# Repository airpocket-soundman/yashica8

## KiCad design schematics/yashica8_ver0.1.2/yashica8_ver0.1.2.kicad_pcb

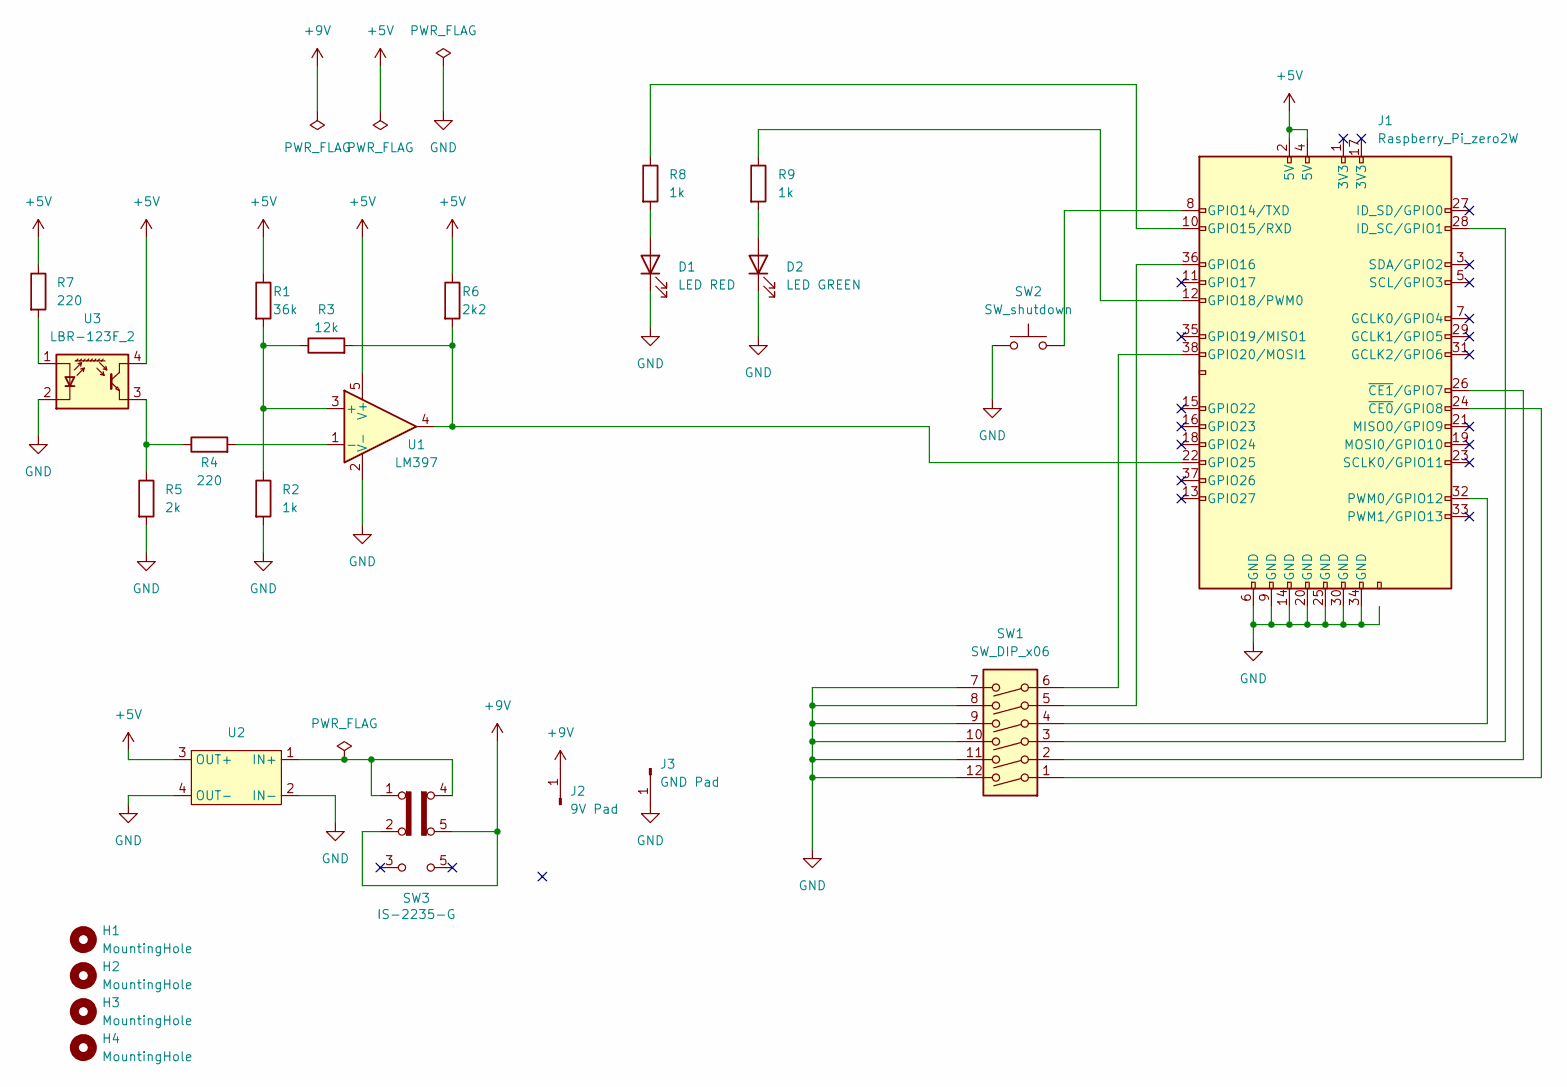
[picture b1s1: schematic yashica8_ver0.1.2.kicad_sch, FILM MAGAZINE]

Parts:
D1: LED RED; LED_D3.0mm
D2: LED GREEN; LED_D3.0mm
H1, H2, H3, H4: MountingHole; MountingHole_2.1mm
J1: Raspberry_Pi_zero2W; raspberry Pi socket 2x19
J2: 9V Pad; SolderWirePad_1x01_SMD_1x2mm
J3: GND Pad; SolderWirePad_1x01_SMD_1x2mm
R1: 36k; R_0805_2012Metric_Pad1.20x1.40mm_HandSolder
R2, R8, R9: 1k; R_0805_2012Metric_Pad1.20x1.40mm_HandSolder
R3: 12k; R_0805_2012Metric_Pad1.20x1.40mm_HandSolder
R4, R7: 220; R_0805_2012Metric_Pad1.20x1.40mm_HandSolder
R5: 2k; R_0805_2012Metric_Pad1.20x1.40mm_HandSolder
R6: 2k2; R_0805_2012Metric_Pad1.20x1.40mm_HandSolder
SW1: SW_DIP_x06; SW_DIP_SPSTx06_Slide_9.78x17.42mm_W7.62mm_P2.54mm
SW2: SW_shutdown; SW_PUSH_6mm
SW3: IS-2235-G
U1: LM397; SOT-23-5
U2: MP2307 DC-DC Board
U3: LBR-123F_2

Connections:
+5V: J1.2 (5V), J1.4 (5V), R1.1, R6.1, R7.1, U1.5 (V+), U2.3 (OUT+), U3.4
+9V: J2.1, SW3.2 (B), SW3.5 (B)
GND: D1.1 (K), D2.1 (K), J1.6 (GND), J1.9 (GND), J1.14 (GND), J1.20 (GND), J1.25 (GND), J1.30 (GND), J1.34 (GND), J3.1, R2.2, R5.2, SW1.7, SW1.8, SW1.9, SW1.10, SW1.11, SW1.12, SW2.1, U1.2 (V-), U2.2 (IN-), U2.4 (OUT-), U3.2 (K)
unnamed: D1.2 (A), R8.2
unnamed: D2.2 (A), R9.2
unnamed: J1.8 (GPIO14/TXD), SW2.2
unnamed: J1.10 (GPIO15/RXD), R8.1
unnamed: J1.36 (GPIO16), SW1.5
unnamed: J1.12 (GPIO18/PWM0), R9.1
unnamed: J1.38 (GPIO20/MOSI1), SW1.6
unnamed: J1.22 (GPIO25), R3.2, R6.2, U1.4
unnamed: J1.28 (ID_SC/GPIO1), SW1.3
unnamed: J1.32 (PWM0/GPIO12), SW1.4
unnamed: J1.24 (~CE0/GPIO8), SW1.1
unnamed: J1.26 (~CE1/GPIO7), SW1.2
unnamed: R4.1, R5.1, U3.3
unnamed: R1.2, R2.1, R3.1, U1.3 (+)
unnamed: R4.2, U1.1 (-)
unnamed: SW3.1 (A), SW3.4 (C), U2.1 (IN+)
unnamed: R7.2, U3.1 (A)

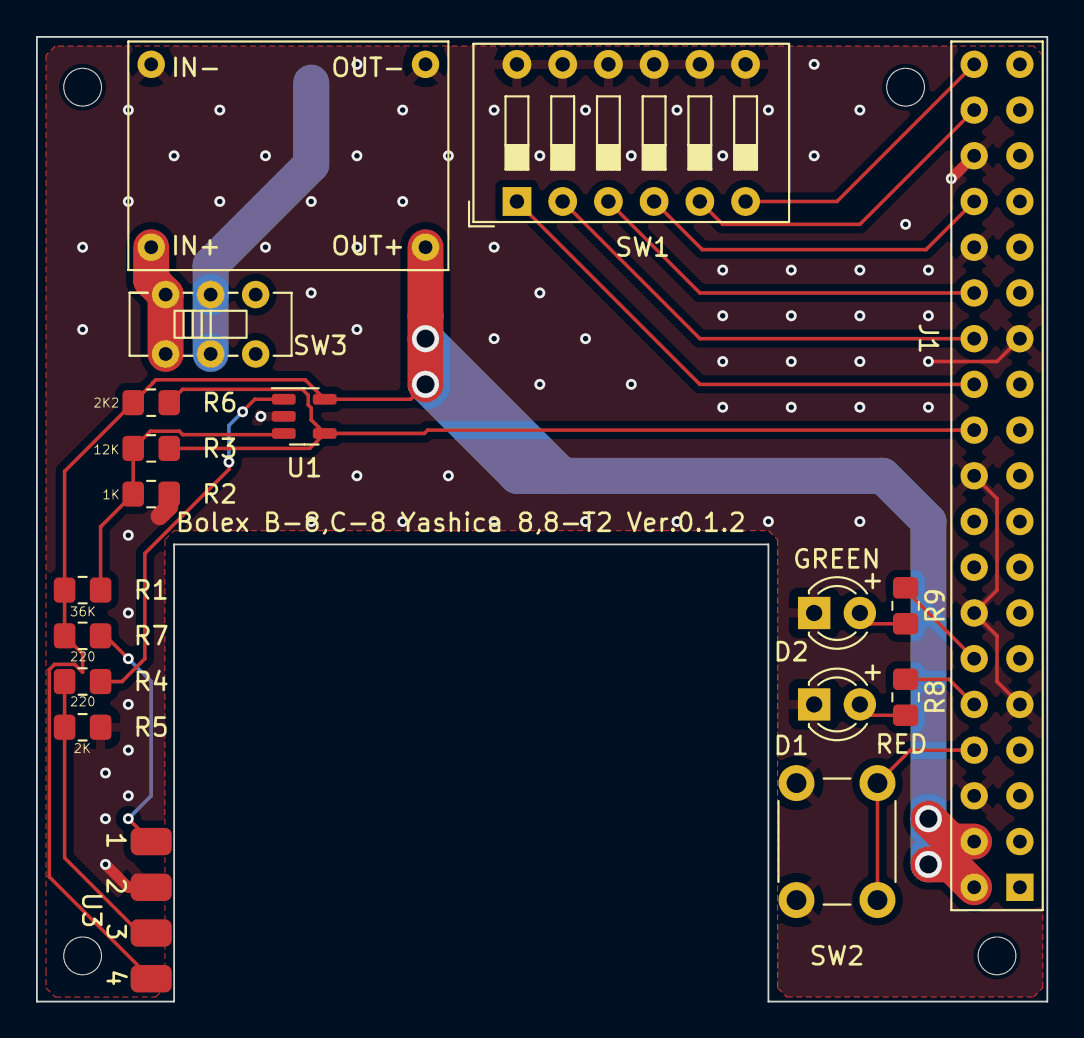
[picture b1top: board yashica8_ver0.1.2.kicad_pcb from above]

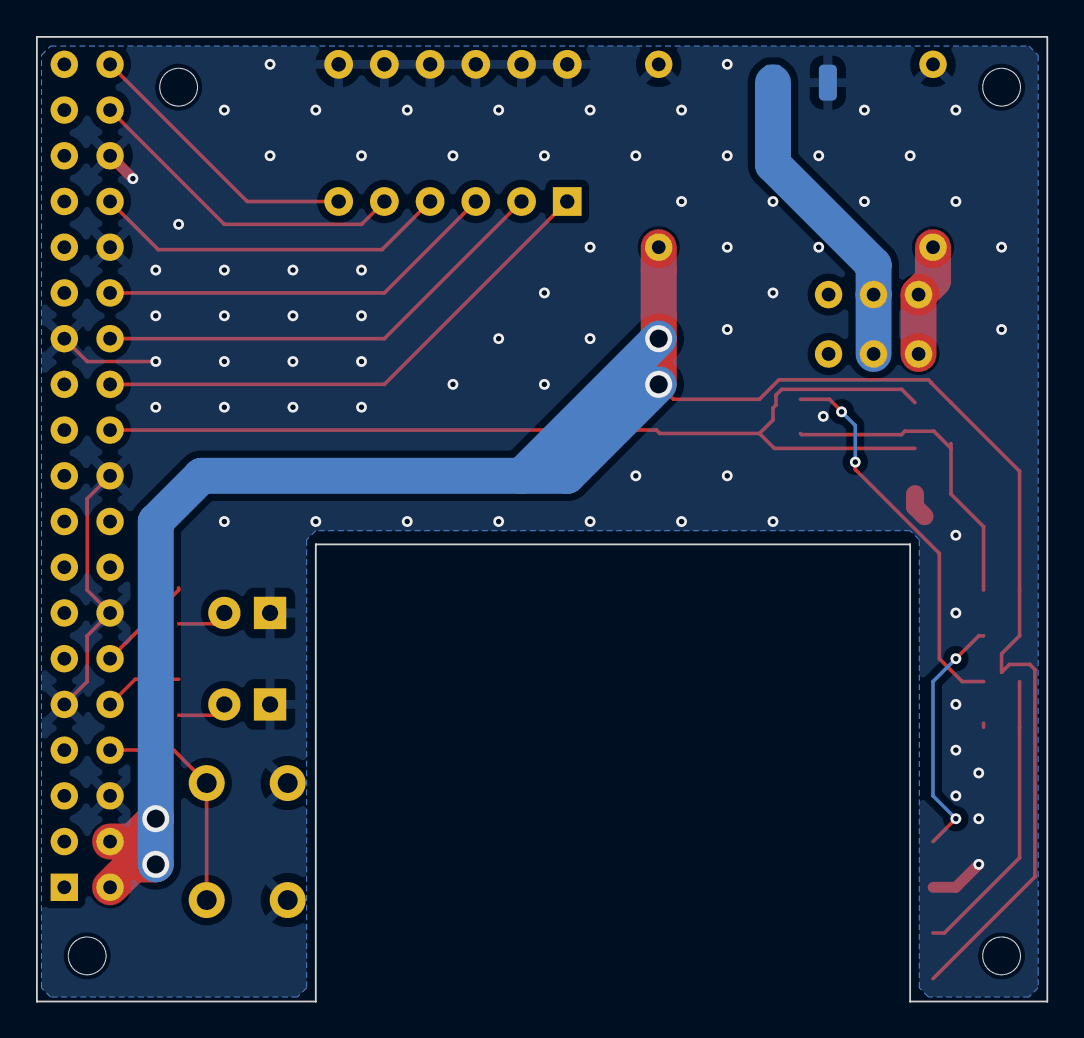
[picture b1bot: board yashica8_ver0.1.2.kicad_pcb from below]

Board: 2 copper layers, 56.1 x 53.6 mm, 24 parts (2 on the bottom side), 20 nets.

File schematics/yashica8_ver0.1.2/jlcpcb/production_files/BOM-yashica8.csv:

Comment,Designator,Footprint,LCSC
LED GREEN,D2,LED_D3.0mm,
SW_shutdown,SW2,SW_PUSH_6mm,
2k,R5,R_0805_2012Metric_Pad1.20x1.40mm_HandSolder,
220,R7,R_0805_2012Metric_Pad1.20x1.40mm_HandSolder,
LM397,U1,SOT-23-5,
Raspberry_Pi_zero2W,J1,raspberry Pi socket 2x19,
1k,R2,R_0805_2012Metric_Pad1.20x1.40mm_HandSolder,
~,U2,MP2307 DC-DC Board,
LED RED,D1,LED_D3.0mm,
36k,R1,R_0805_2012Metric_Pad1.20x1.40mm_HandSolder,
1k,R8,R_0805_2012Metric_Pad1.20x1.40mm_HandSolder,
SW_DIP_x06,SW1,SW_DIP_SPSTx06_Slide_9.78x17.42mm_W7.62mm_P2.54mm,
220,R4,R_0805_2012Metric_Pad1.20x1.40mm_HandSolder,
2k2,R6,R_0805_2012Metric_Pad1.20x1.40mm_HandSolder,
LBR-123F_2,U3,LBR-123F_2,
12k,R3,R_0805_2012Metric_Pad1.20x1.40mm_HandSolder,
1k,R9,R_0805_2012Metric_Pad1.20x1.40mm_HandSolder,

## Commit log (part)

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2024-09-23 projcet
2024-09-23 add stls
2024-09-23 add schematic
